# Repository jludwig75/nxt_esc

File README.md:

# nxt_esc
This project is for an ESC for connecting an RC receiver and an ordinary RC battery to Lego Mindstorms NXT motors. I took ideas from Wayne and Layne's Bricktronics shield. I am not an electrical engineer, so if you like this idea and know how to improve it, pleas let me know.

Materials
- 1 Arduino Pro Mini
- 1 L293A motor driver
- 1 100 uF capacitor
- 1 0.1 uF capacitor
- 1 47 uF capacitor
- 1 LM7805 5V Voltage vregulator
- 1 SPDT slider switch
- 1 trim pot
- 2 100k ohm resistors
- 2 NXT jacks from Wayne and Layne

The PCB is about 0.3 mm smaller in size than a 6x6 Lego plate. This allows it to fit in an 8x8 Lego box. I would recommend using bricks with Technics holes for the sides without controls. This will provide a way to connect it to other NXT/Technics Lego bricks.

Still need to figure out:
- Do I need separate smoothing capacitors for the L293D, the receiver, the arduino and the 4.3 V connections to the NXT motors? I think it won't hurt, but it takes up more space. I designed it with one set of smoothing capacitors for all devices, but the motor driver motor voltage input.
- I think it's OK to have the LM7085 output go to the arduino VIN. That makes two voltage requlators in series to the pro mini. The specs say 5V is enough power and forum posts suggest even 4.5V is enough.
- I have the 5V to the receiver, the L293D and the NXT motors coming off of of the LM7085 so that the arduino GPIO pins don't have to power them. Is this good? Is it necessary?
- The Bricktronics shield uses 100 uF and 0.1 uF capacitors together for noise smoothing and power spike protection. Is this a good idea for all components?
- I have a lot of crossing traces. Some lines are PWM signals. Do I need to do anything with routing my traces to avoid interference? I think the frequencies are too low to worry about.
- Although the Arduino can handle up to 12 V input, I read some forum posts that the internal regulator can get hot if used on a 7.2/7.4 volt battery so I added an external regulator. Do I need to do this? Would it be better to use a switching power supply instead?
- Should I use an EC3 or some other common battery jack or just screw terminals? I think screw terminals are nice, because they come off the side and will be lower profile. The screw terminal would also allow a longer overcall connection when connected to the battery.
- It looks like the receiver I have and most receivers have a steering sensitivity/range setting. If so, I can eliminate the steering sensitivity knob.

If you have any answers to my questions or suggestions, email me at jr.ludwig@gmail.com.

TODO:
- Fix up the PCB labels for the steering sensitivity knob and the receiver connection.
- Move the NXT jacks and steering type switch so that small Lego bricks can be used to hold that end of the board in a Lego box and still allow access to them. I need to print out the schematic and measure it against Lego bricks to see. This may not be necessary, because I can use 1x6 strips at the bottom and top of the opening to hold it in place.

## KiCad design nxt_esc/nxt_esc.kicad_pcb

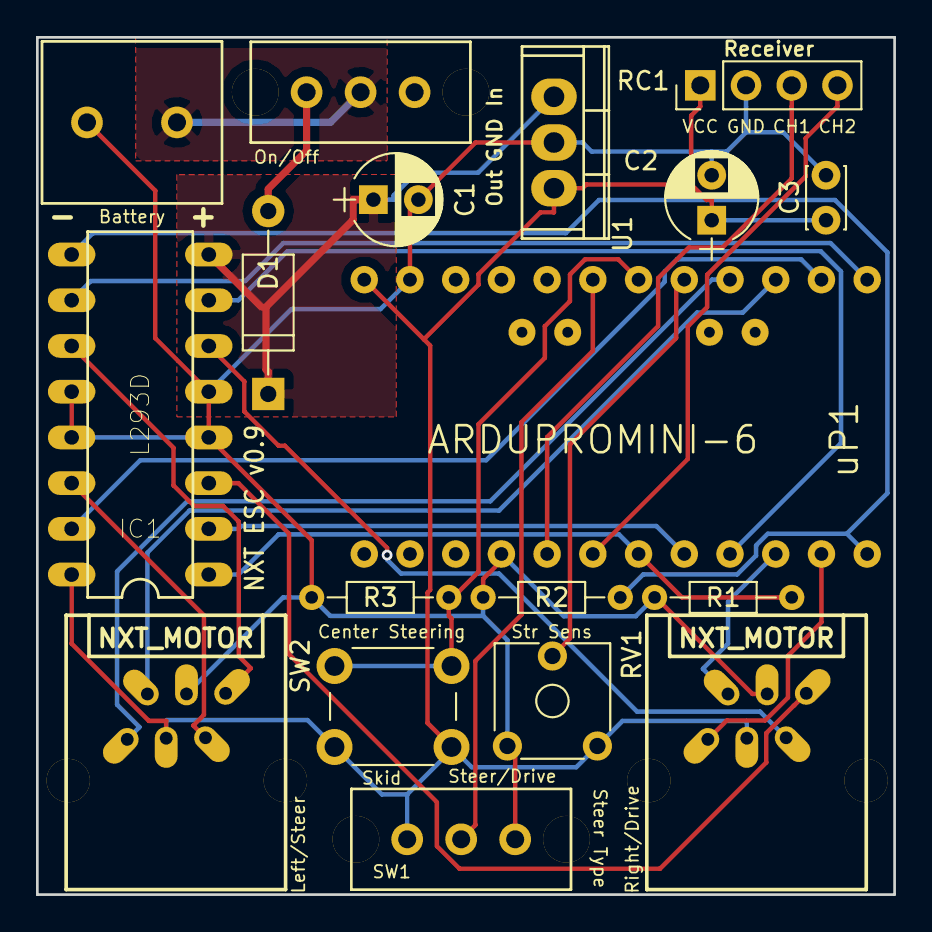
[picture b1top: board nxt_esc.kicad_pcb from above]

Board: 2 copper layers, 47.6 x 47.6 mm, 18 parts (0 on the bottom side), 24 nets.

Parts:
Battery: Battery; SCREW_TERMINAL_JRL
C1: 47u; CP_Radial_D5.0mm_P2.50mm
C2: 100u; CP_Radial_D5.0mm_P2.50mm
C3: 0.1 u; C_Disc_D3.4mm_W2.1mm_P2.50mm
D1: D_Schottky; D_A-405_P10.16mm_Horizontal
IC1: L293D; DIL16
J1, J2: NXT_MOTOR; WNL_NXT_SOCKET
On/Off: Power; SLIDE_SWITCH_JRL
R1, R2, R3: 100k; R_Axial_DIN0204_L3.6mm_D1.6mm_P7.62mm_Horizontal
RC1: RC_Receiver; Pin_Header_Straight_1x04_Pitch2.54mm
RV1: Steering Sensitivity; Potentiometer_Trimmer_ACP_CA6v_Horizontal
SW1: Skid Steer/Drive & Steer; SLIDE_SWITCH_JRL
SW2: Center Steering; SW_PUSH_6mm
U1: LM7805CT; TO-220
uP1: ARDUPROMINI-6; ArduProMini-6

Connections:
GND: Battery.2, C1.2, C2.2, C3.2, IC1.4, IC1.5, IC1.12, IC1.13, J1.3, J2.3, R1.1, R2.2, R3.1, RC1.2, RV1.3, SW1.3, U1.2, uP1.10, uP1.20
unnamed: Battery.1, On/Off.2
unnamed: C2.1, C3.1, IC1.16, J1.4, J2.4, RC1.1, RV1.1, SW1.1, SW2.2, U1.3, uP1.19
unnamed: D1.2, On/Off.1
unnamed: IC1.1, R1.2, uP1.13
unnamed: IC1.2, uP1.14
unnamed: IC1.3, J1.1
unnamed: IC1.6, J1.2
unnamed: IC1.7, uP1.15
unnamed: IC1.9, R2.1, uP1.18
unnamed: IC1.10, uP1.30
unnamed: IC1.11, J2.1
unnamed: IC1.14, J2.2
unnamed: IC1.15, uP1.29
unnamed: J1.5, uP1.16
unnamed: J1.6, uP1.17
unnamed: J2.5, uP1.28
unnamed: J2.6, uP1.27
unnamed: R3.2, SW2.1, uP1.25
unnamed: RC1.3, uP1.11
unnamed: RC1.4, uP1.12
unnamed: RV1.2, uP1.26
unnamed: SW1.2, uP1.24
VCC: C1.1, D1.1, IC1.8, U1.1

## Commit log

2018-01-10 Created repo
2018-01-10 Generated image of schematic
2018-01-10 Changed schematic
2018-01-11 Updated schematic picture
2018-01-11 Added smoothing capacitors
2018-01-11 Updated PCB
2018-01-11 Added image of PCB
2018-01-11 Resized board to 6x6 Lego size
2018-03-14 Added center steering button
2018-03-14 Generated gerber file
2018-03-14 Updated images
2018-03-15 Added motor jack labels. Forgot to route wires.
2018-03-16 Added reverse polarity protection diode and power switch
2018-03-22 Updated components to ones I already have
2018-03-22 Rotated NXT jacks
2018-04-13 Started adding wider traces
2018-04-14 Revert "Started adding wider traces"
    This reverts commit 0565dbcc7c240f27c084cab386e32b7ff774fa91.
2018-04-14 Made more room for arduino
2018-09-27 Added planes for ground and power
